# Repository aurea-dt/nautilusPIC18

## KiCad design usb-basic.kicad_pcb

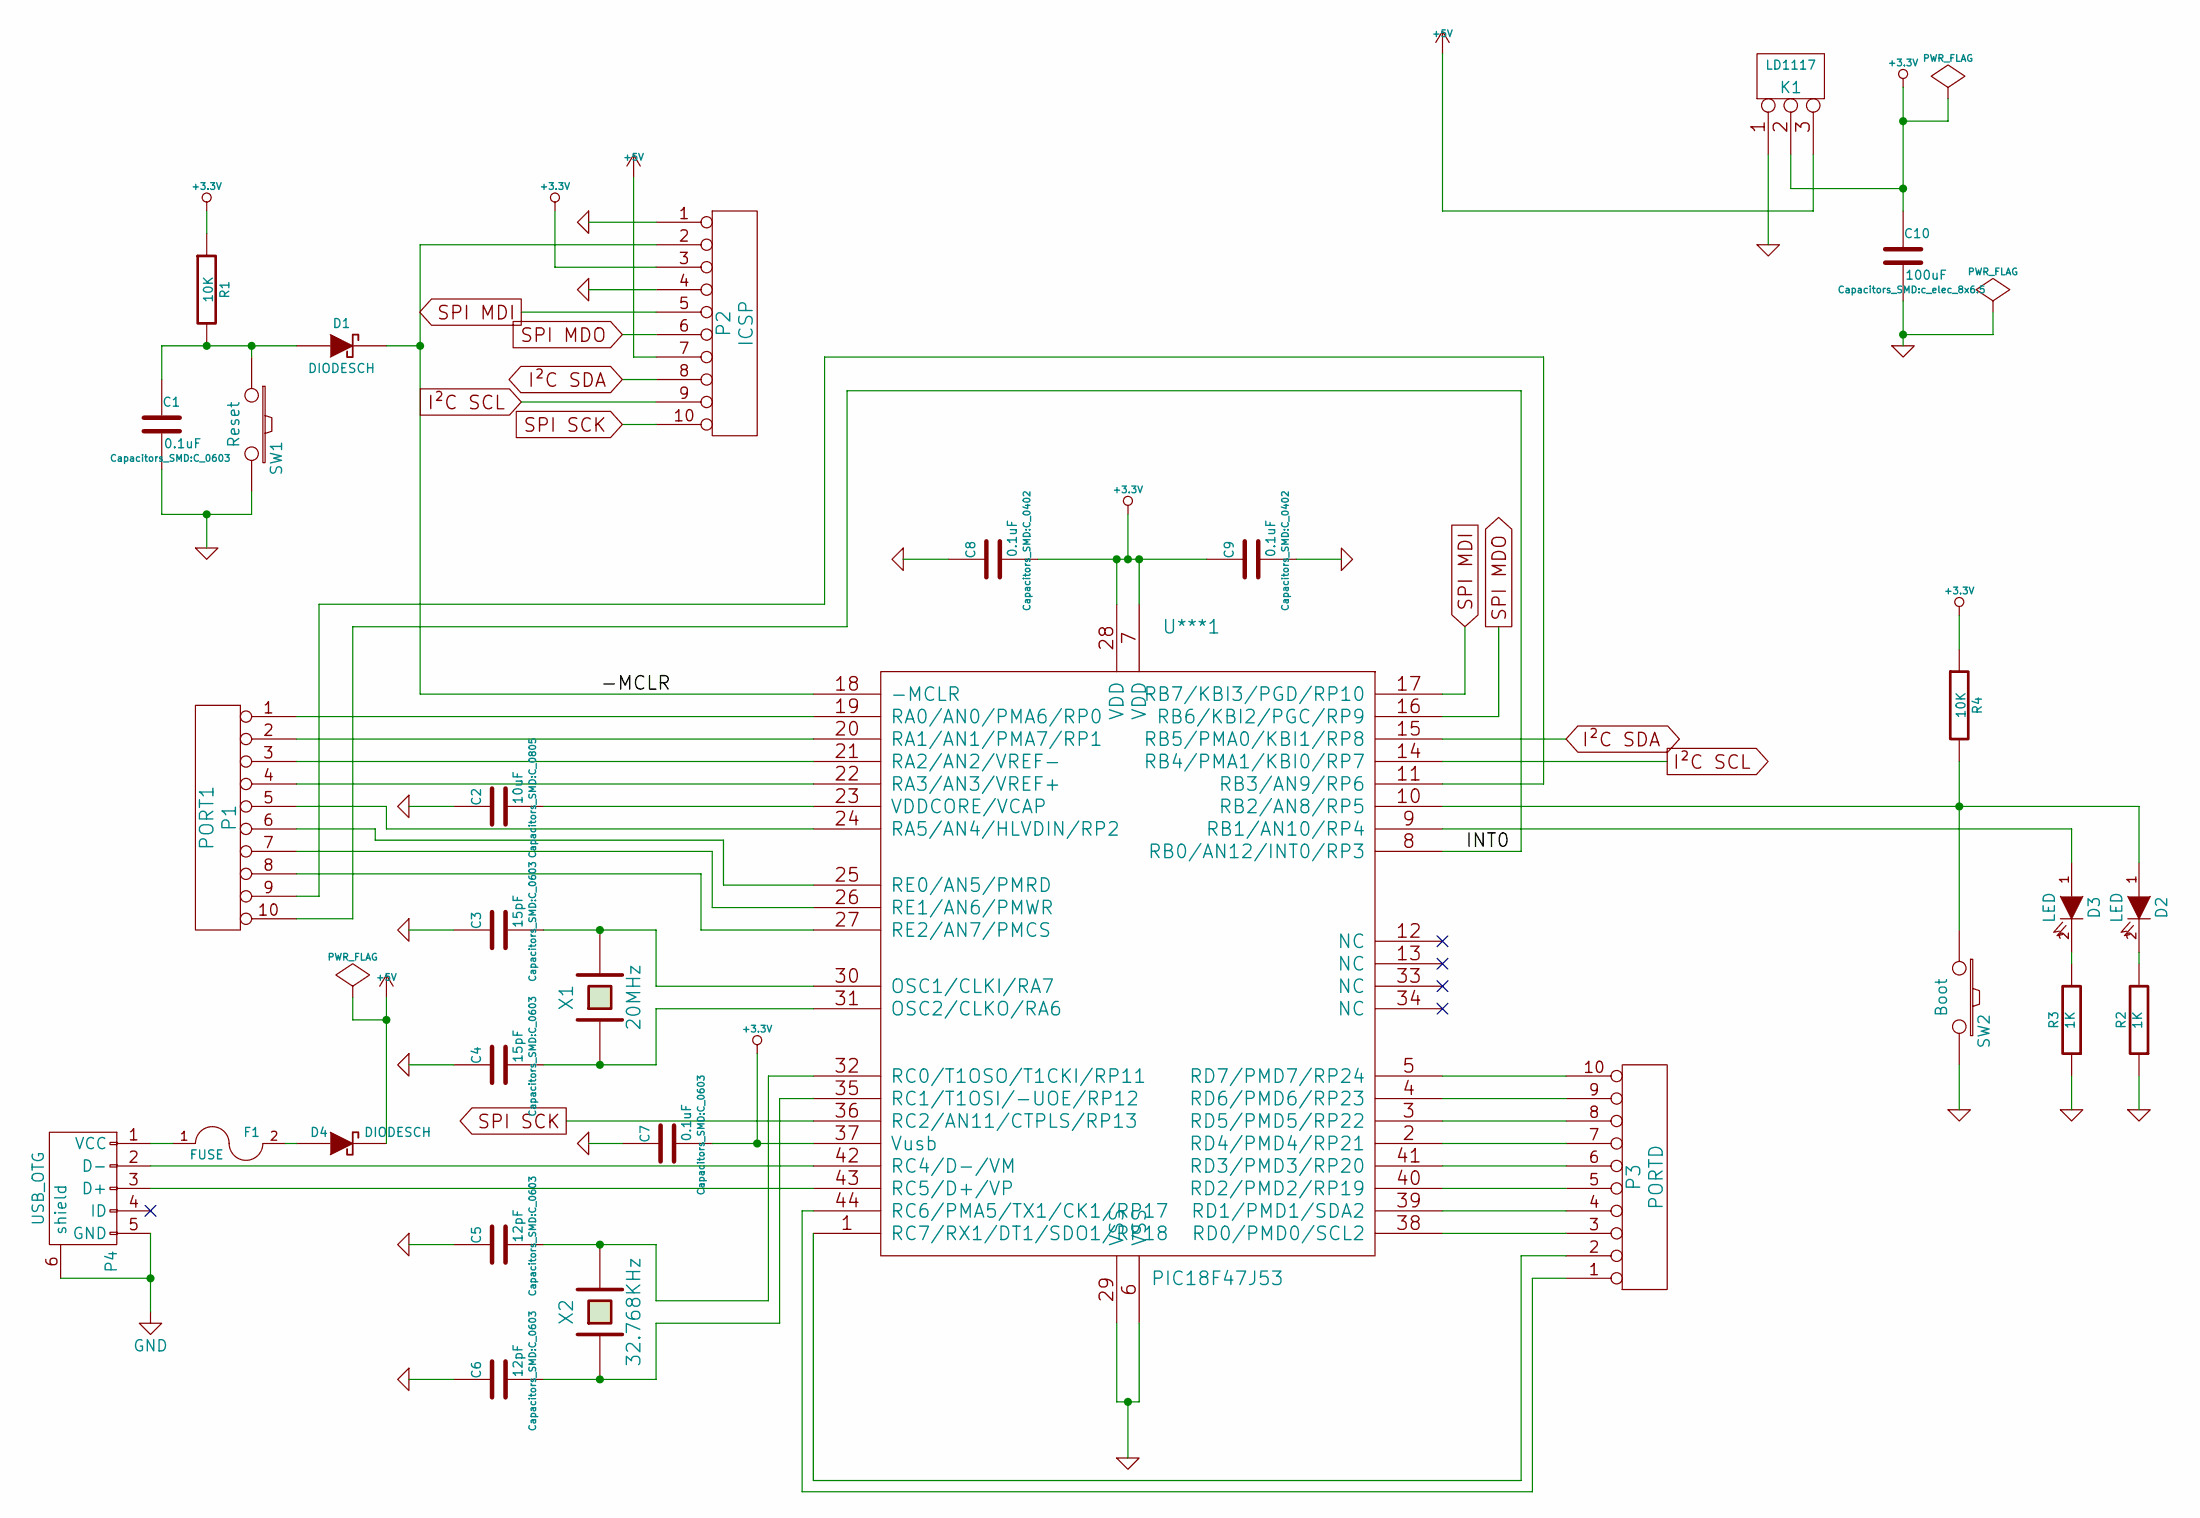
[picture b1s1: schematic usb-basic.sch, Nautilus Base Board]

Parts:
C1, C7: 0.1uF; C_0603
C2: 10uF; C_0805
C3, C4: 15pF; C_0603
C5, C6: 12pF; C_0603
C8, C9: 0.1uF; C_0402
C10: 100uF; c_elec_8x6.5
D1, D4: DIODESCH; sod123
D2, D3: LED; LED-0805
F1: FUSE; Fuse_SMD1206_Reflow
K1: LD1117; sot223
P1: PORT1; pin_socket_10
P2: ICSP; pin_socket_10
P3: PORTD; pin_socket_10
P4: USB_OTG; USB_Mini-B
R1, R4: 10K; R_0603
R2, R3: 1K; R_0603
SW1: Reset; SW_SPST_EVQP7A
SW2: Boot; SW_SPST_EVQP7A
U***1: PIC18F47J53; lqfp44
X1: 20MHz; Q_49U3HMS
X2: 32.768KHz; R_1206

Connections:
+3.3V: C7.2, C8.2, C9.1, C10.1, K1.2 (PM), P2.3, R1.1, R4.1, U***1.7 (VDD), U***1.28 (VDD), U***1.37 (Vusb)
+5V: D4.2 (K), K1.3, P2.7
/-MCLR: D1.2 (K), P2.2, U***1.18 (-MCLR)
/INT0: P1.10, U***1.8 (RB0/AN12/INT0/RP3)
GND: C1.2, C2.1, C3.1, C4.1, C5.1, C6.1, C7.1, C8.1, C9.2, C10.2, K1.1, P2.1, P2.4, P4.5 (GND), P4.6 (shield), R2.1, R3.1, SW1.2, SW2.2, U***1.6 (VSS), U***1.29 (VSS); also elsewhere on the board
I²C SCL: P2.9, U***1.14 (RB4/PMA1/KBI0/RP7)
I²C SDA: P2.8, U***1.15 (RB5/PMA0/KBI1/RP8)
unnamed: C1.1, D1.1 (A), R1.2, SW1.1
unnamed: C2.2, U***1.23 (VDDCORE/VCAP)
unnamed: C3.2, U***1.30 (OSC1/CLKI/RA7), X1.2
unnamed: C4.2, U***1.31 (OSC2/CLKO/RA6), X1.1
unnamed: C5.2, U***1.32 (RC0/T1OSO/T1CKI/RP11), X2.2
unnamed: C6.2, U***1.35 (RC1/T1OSI/-UOE/RP12), X2.1
unnamed: D2.1 (A), R4.2, SW2.1, U***1.10 (RB2/AN8/RP5)
unnamed: D2.2 (K), R2.2
unnamed: D3.1 (A), U***1.9 (RB1/AN10/RP4)
unnamed: D3.2 (K), R3.2
unnamed: D4.1 (A), F1.2
unnamed: F1.1, P4.1 (VCC)
unnamed: P1.1, U***1.19 (RA0/AN0/PMA6/RP0)
unnamed: P1.2, U***1.20 (RA1/AN1/PMA7/RP1)
unnamed: P1.3, U***1.21 (RA2/AN2/VREF-)
unnamed: P1.4, U***1.22 (RA3/AN3/VREF+)
unnamed: P1.5, U***1.24 (RA5/AN4/HLVDIN/RP2)
unnamed: P1.6, U***1.25 (RE0/AN5/PMRD)
unnamed: P1.7, U***1.26 (RE1/AN6/PMWR)
unnamed: P1.8, U***1.27 (RE2/AN7/PMCS)
unnamed: P1.9, U***1.11 (RB3/AN9/RP6)
unnamed: P3.1, U***1.44 (RC6/PMA5/TX1/CK1/RP17)
unnamed: P3.2, U***1.1 (RC7/RX1/DT1/SDO1/RP18)
unnamed: P3.3, U***1.38 (RD0/PMD0/SCL2)
unnamed: P3.4, U***1.39 (RD1/PMD1/SDA2)
unnamed: P3.5, U***1.40 (RD2/PMD2/RP19)
unnamed: P3.6, U***1.41 (RD3/PMD3/RP20)
unnamed: P3.7, U***1.2 (RD4/PMD4/RP21)
unnamed: P3.8, U***1.3 (RD5/PMD5/RP22)
unnamed: P3.9, U***1.4 (RD6/PMD6/RP23)
unnamed: P3.10, U***1.5 (RD7/PMD7/RP24)
unnamed: P4.2 (D-), U***1.42 (RC4/D-/VM)
unnamed: P4.3 (D+), U***1.43 (RC5/D+/VP)
SPI MDI: P2.5, U***1.17 (RB7/KBI3/PGD/RP10)
SPI MDO: P2.6, U***1.16 (RB6/KBI2/PGC/RP9)
SPI SCK: P2.10, U***1.36 (RC2/AN11/CTPLS/RP13)

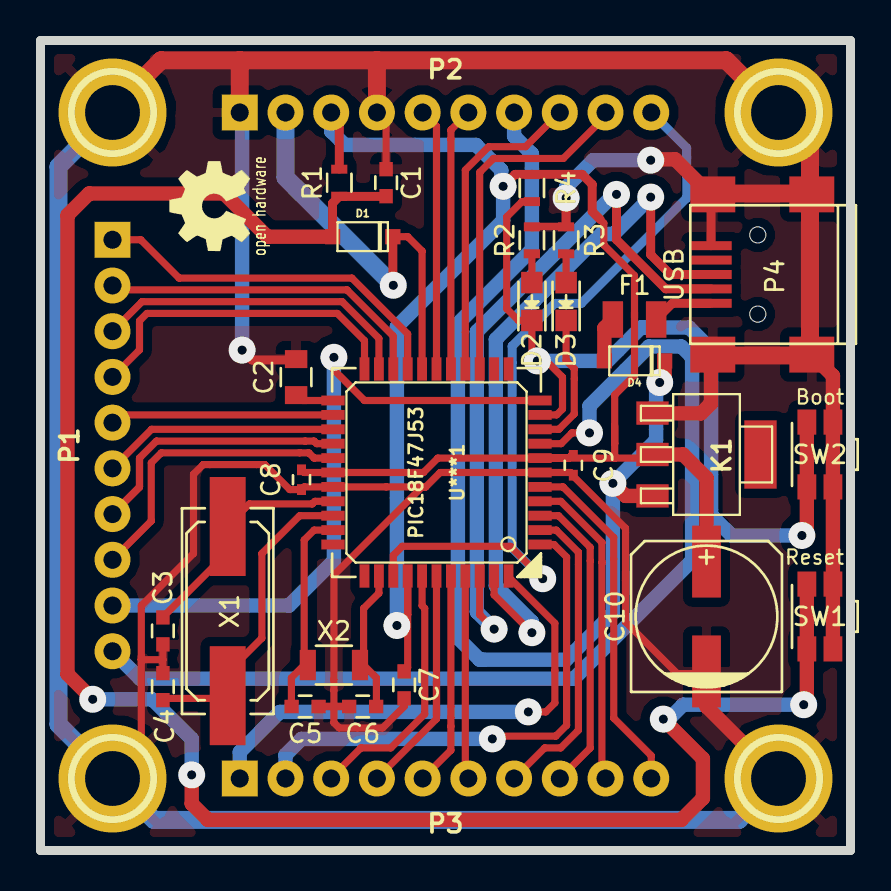
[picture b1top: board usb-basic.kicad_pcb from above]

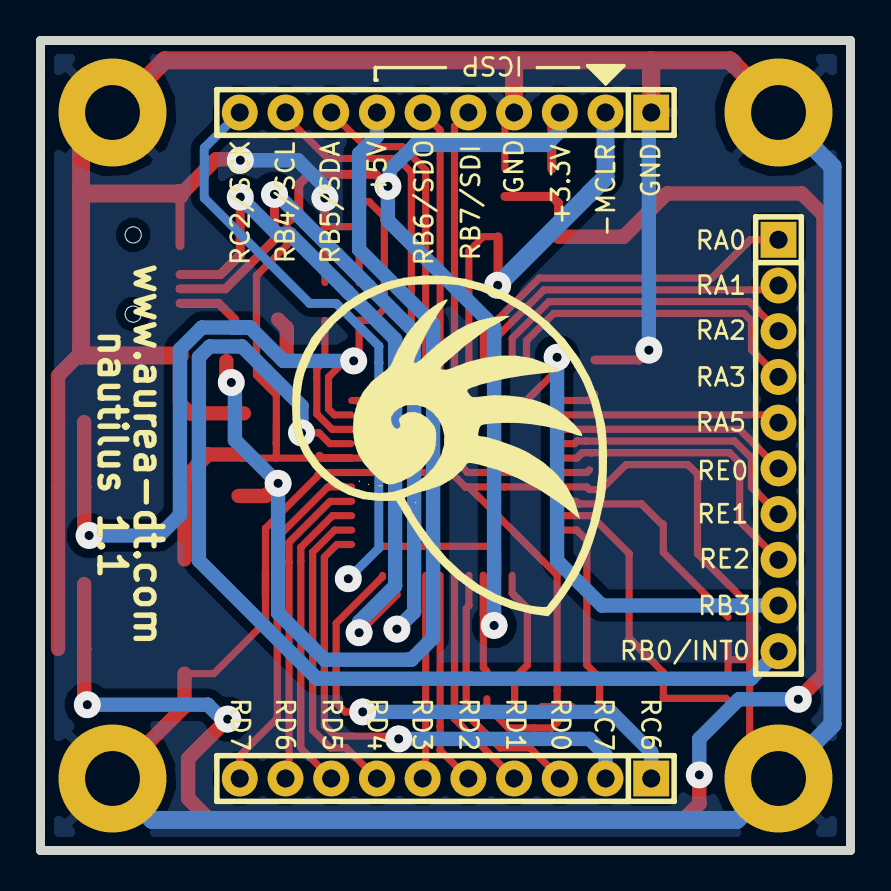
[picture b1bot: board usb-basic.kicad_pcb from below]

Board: 2 copper layers, 45.0 x 45.0 mm, 33 parts (3 on the bottom side), 43 nets.

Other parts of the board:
1PIN, 1PIN#2, 1PIN#3, 1PIN#4: P***; 1pin

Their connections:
GND: 1PIN.1, 1PIN#2.1, 1PIN#3.1, 1PIN#4.1; also elsewhere on the board
